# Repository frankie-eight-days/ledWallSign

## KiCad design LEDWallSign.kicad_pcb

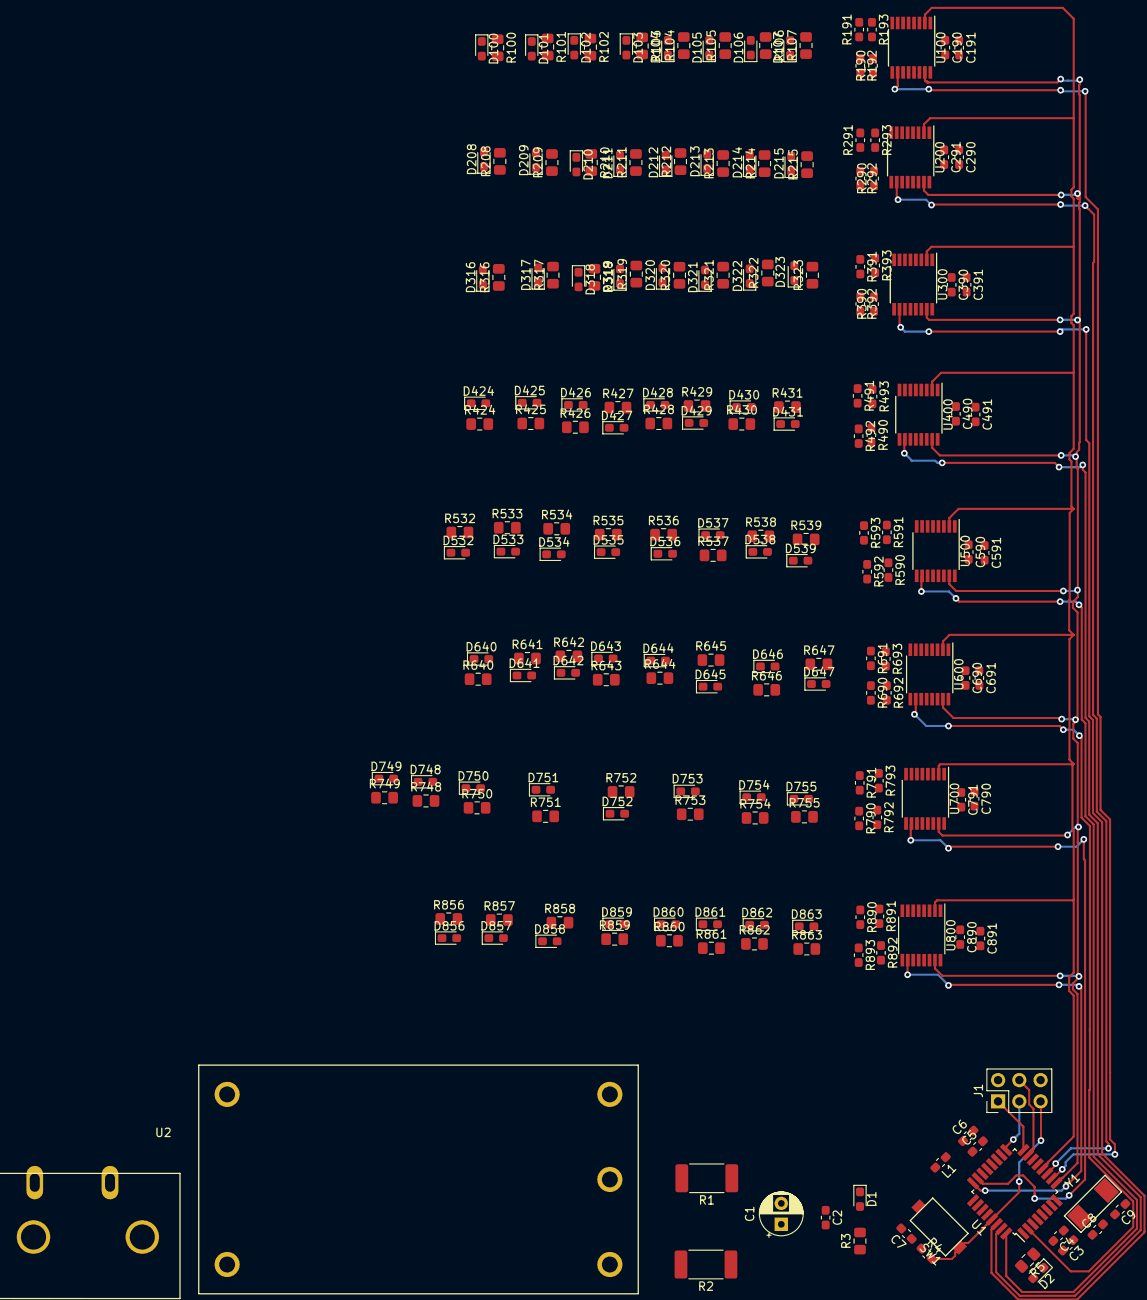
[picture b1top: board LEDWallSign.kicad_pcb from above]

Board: 2 copper layers, 207 parts (0 on the bottom side), 170 nets.

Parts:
C1: 10u; CP_Radial_D5.0mm_P2.50mm
C2, C4, C5, C7, C191, C291, C391, C491, C591, C691, C791, C891: 100nF; C_0603_1608Metric_Pad1.05x0.95mm_HandSolder
C3, C190, C290, C390, C490, C590, C690, C790, C890: 1uF; C_0603_1608Metric_Pad1.05x0.95mm_HandSolder
C6: 100pF; C_0603_1608Metric_Pad1.05x0.95mm_HandSolder
C8, C9: 18pF; C_0603_1608Metric_Pad1.05x0.95mm_HandSolder
D1, D2, D100, D101, D102, D103, D104, D105, D106, D107, D208, D209, D210, D211, D212, D213, D214, D215, D316, D317, D318, D319, D320, D321, D322, D323, D424, D425, D426, D427, D428, D429, D430, D431, D532, D533, D534, D535, D536, D537, D538, D539, D640, D641, D642, D643, D644, D645, D646, D647, D748, D749, D750, D751, D752, D753, D754, D755, D856, D857, D858, D859, D860, D861, D862, D863: LED; LED_0603_1608Metric_Pad1.05x0.95mm_HandSolder
J1: ISP Header; PinHeader_2x03_P2.54mm_Vertical
L1: Ferrite_Bead; L_0603_1608Metric_Pad1.05x0.95mm_HandSolder
P1: Conn_WallPlug; Qualtek 770W-X2
R1, R2: 0; R_2512_6332Metric_Pad1.52x3.35mm_HandSolder
R3, R5, R100, R101, R102, R103, R104, R105, R106, R107, R208, R209, R210, R211, R212, R213, R214, R215, R316, R317, R318, R319, R320, R321, R322, R323, R424, R425, R426, R427, R428, R429, R430, R431, R532, R533, R534, R535, R536, R537, R538, R539, R640, R641, R642, R643, R644, R645, R646, R647, R748, R749, R750, R751, R752, R753, R754, R755, R856, R857, R858, R859, R860, R861, R862, R863: 1k; R_0805_2012Metric_Pad1.15x1.40mm_HandSolder
R4, R190, R193, R290, R293, R390, R393, R490, R493, R590, R593, R690, R693, R790, R793, R890, R893: 10k; R_0603_1608Metric_Pad1.05x0.95mm_HandSolder
R191, R192, R291, R292, R391, R392, R491, R492, R591, R592, R691, R692, R791, R792, R891, R892: DNP; R_0603_1608Metric_Pad1.05x0.95mm_HandSolder
SW1: KSR251GLFS
U1: ATmega328-AU; TQFP-32_7x7mm_P0.8mm
U2: RAC10-05SK
U100, U200, U300, U400, U500, U600, U700, U800: TLC6C598-Q1; TSSOP-16_4.4x5mm_P0.65mm
Y1: 8MHz; ECS-23G

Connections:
+5V: C1.1, C2.2, C3.1, C4.1, C7.1, C190.1, C191.1, C290.1, C291.1, C390.1, C391.1, C490.1, C491.1, C590.1, C591.1, C690.1, C691.1, C790.1, C791.1, C890.1, C891.1, J1.2, L1.2, R2.1, R3.1, R4.1, R100.1, R101.1, R102.1, R103.1, R104.1, R105.1, R106.1, R107.1, R190.1, R191.1, R208.1, R209.1, R210.1, R211.1, R212.1, R213.1, R214.1, R215.1, R290.1, R291.1, R316.1, R317.1, R318.1, R319.1, R320.1, R321.1, R322.1, R323.1, R390.1, R391.1, R424.1, R425.1, R426.1, R427.1, R428.1, R429.1, R430.1, R431.1, R490.1, R491.1, R532.1, R533.1, R534.1, R535.1, R536.1, R537.1, R538.1, R539.1, R590.1, R591.1, R640.1, R641.1, R642.1, R643.1, R644.1, R645.1, R646.1, R647.1, R690.1, R691.1, R748.1, R749.1, R750.1, R751.1, R752.1, R753.1, R754.1, R755.1, R790.1, R791.1, R856.1, R857.1, R858.1, R859.1, R860.1, R861.1, R862.1, R863.1, R890.1, R891.1, U1.4, U1.6, U100.1, U200.1, U300.1, U400.1, U500.1, U600.1, U700.1, U800.1
+5VA: C5.1, C6.1, L1.1, U1.18, U1.20
/MISO: J1.1, U1.16
/MOSI: J1.4, U1.15
/SCK: J1.3, U1.17
/XTAL_IN: C8.1, U1.7, Y1.1
/XTAL_OUT: C9.1, U1.8, Y1.2
/blinky: R5.1, U1.1
/clockPin: U1.9, U100.15, U200.15, U300.15, U400.15, U500.15, U600.15, U700.15, U800.15
/dataPin: U1.12, U100.2, U200.2, U300.2, U400.2, U500.2, U600.2, U700.2, U800.2
/latch1: U1.10, U100.10
/latch2: U1.11, U200.10
/latch3: U1.30, U300.10
/latch4: U1.31, U400.10
/latch5: U1.32, U500.10
/latch6: U1.2, U600.10
/latch7: U1.23, U700.10
/latch8: U1.24, U800.10
/led0: D100.1, U100.3
/led1: D101.1, U100.4
/led2: D102.1, U100.5
/led3: D103.1, U100.6
/led4: D104.1, U100.11
/led5: D105.1, U100.12
/led6: D106.1, U100.13
/led7: D107.1, U100.14
/led8: D208.1, U200.3
/led9: D209.1, U200.4
/led10: D210.1, U200.5
/led11: D211.1, U200.6
/led12: D212.1, U200.11
/led13: D213.1, U200.12
/led14: D214.1, U200.13
/led15: D215.1, U200.14
/led16: D316.1, U300.3
/led17: D317.1, U300.4
/led18: D318.1, U300.5
/led19: D319.1, U300.6
/led20: D320.1, U300.11
/led21: D321.1, U300.12
/led22: D322.1, U300.13
/led23: D323.1, U300.14
/led24: D424.1, U400.3
/led25: D425.1, U400.4
/led26: D426.1, U400.5
/led27: D427.1, U400.6
/led28: D428.1, U400.11
/led29: D429.1, U400.12
/led30: D430.1, U400.13
/led31: D431.1, U400.14
/led32: D532.1, U500.3
/led33: D533.1, U500.4
/led34: D534.1, U500.5
/led35: D535.1, U500.6
/led36: D536.1, U500.11
/led37: D537.1, U500.12
/led38: D538.1, U500.13
/led39: D539.1, U500.14
/led40: D640.1, U600.3
/led41: D641.1, U600.4
/led42: D642.1, U600.5
/led43: D643.1, U600.6
/led44: D644.1, U600.11
/led45: D645.1, U600.12
/led46: D646.1, U600.13
/led47: D647.1, U600.14
/led48: D748.1, U700.3
/led49: D749.1, U700.4
/led50: D750.1, U700.5
/led51: D751.1, U700.6
/led52: D752.1, U700.11
/led53: D753.1, U700.12
/led54: D754.1, U700.13
/led55: D755.1, U700.14
/led56: D856.1, U800.3
/led57: D857.1, U800.4
/led58: D858.1, U800.5
/led59: D859.1, U800.6
/led60: D860.1, U800.11
/led61: D861.1, U800.12
/led62: D862.1, U800.13
/led63: D863.1, U800.14
/~RESET: J1.5, R4.2, SW1.1, U1.29
GND: C1.2, C2.1, C3.2, C4.2, C5.2, C6.2, C7.2, C8.2, C9.2, C190.2, C191.2, C290.2, C291.2, C390.2, C391.2, C490.2, C491.2, C590.2, C591.2, C690.2, C691.2, C790.2, C791.2, C890.2, C891.2, D1.1, D2.1, J1.6, R1.1, R192.2, R193.2, R292.2, R293.2, R392.2, R393.2, R492.2, R493.2, R592.2, R593.2, R692.2, R693.2, R792.2, R793.2, R892.2, R893.2, SW1.2, U1.3, U1.5, U1.21, U100.16, U200.16, U300.16, U400.16, U500.16, U600.16, U700.16, U800.16
unnamed: D1.2, R3.2
unnamed: D2.2, R5.2
unnamed: D100.2, R100.2
unnamed: D101.2, R101.2
unnamed: D102.2, R102.2
unnamed: D103.2, R103.2
unnamed: D104.2, R104.2
unnamed: D105.2, R105.2
unnamed: D106.2, R106.2
unnamed: D107.2, R107.2
unnamed: D208.2, R208.2
unnamed: D209.2, R209.2
unnamed: D210.2, R210.2
unnamed: D211.2, R211.2
unnamed: D212.2, R212.2
unnamed: D213.2, R213.2
unnamed: D214.2, R214.2
unnamed: D215.2, R215.2
unnamed: D316.2, R316.2
unnamed: D317.2, R317.2
unnamed: D318.2, R318.2
unnamed: D319.2, R319.2
unnamed: D320.2, R320.2
unnamed: D321.2, R321.2
unnamed: D322.2, R322.2
unnamed: D323.2, R323.2
unnamed: D424.2, R424.2
unnamed: D425.2, R425.2
unnamed: D426.2, R426.2
unnamed: D427.2, R427.2
unnamed: D428.2, R428.2
unnamed: D429.2, R429.2
unnamed: D430.2, R430.2
unnamed: D431.2, R431.2
unnamed: D532.2, R532.2
unnamed: D533.2, R533.2
unnamed: D534.2, R534.2
unnamed: D535.2, R535.2
unnamed: D536.2, R536.2
unnamed: D537.2, R537.2
unnamed: D538.2, R538.2
unnamed: D539.2, R539.2
unnamed: D640.2, R640.2
unnamed: D641.2, R641.2
unnamed: D642.2, R642.2
unnamed: D643.2, R643.2
unnamed: D644.2, R644.2
unnamed: D645.2, R645.2
unnamed: D646.2, R646.2
unnamed: D647.2, R647.2
unnamed: D748.2, R748.2
unnamed: D749.2, R749.2
unnamed: D750.2, R750.2
unnamed: D751.2, R751.2
unnamed: D752.2, R752.2
unnamed: D753.2, R753.2
unnamed: D754.2, R754.2
unnamed: D755.2, R755.2
unnamed: D856.2, R856.2
unnamed: D857.2, R857.2
unnamed: D858.2, R858.2
unnamed: D859.2, R859.2
unnamed: D860.2, R860.2
unnamed: D861.2, R861.2
unnamed: D862.2, R862.2
unnamed: D863.2, R863.2
unnamed: P1.1, U2.2
unnamed: P1.2, U2.1
unnamed: R1.2, U2.4
unnamed: R2.2, U2.5
unnamed: R190.2, R192.1, U100.7
unnamed: R191.2, R193.1, U100.8
unnamed: R290.2, R292.1, U200.7
unnamed: R291.2, R293.1, U200.8
unnamed: R390.2, R392.1, U300.7
unnamed: R391.2, R393.1, U300.8
unnamed: R490.2, R492.1, U400.7
unnamed: R491.2, R493.1, U400.8
unnamed: R590.2, R592.1, U500.7
unnamed: R591.2, R593.1, U500.8
unnamed: R690.2, R692.1, U600.7
unnamed: R691.2, R693.1, U600.8
unnamed: R790.2, R792.1, U700.7
unnamed: R791.2, R793.1, U700.8
unnamed: R890.2, R892.1, U800.7
unnamed: R891.2, R893.1, U800.8

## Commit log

2019-08-04 First commit
    Basic schematic done. Need to add footprints, references and complete BOM.
2019-08-05 References and footprints completed. Added back up layout (of components sorted)
    Going to play around with the layout now. Eventually hope to get final one done by end of this week.
2019-08-05 Fully organized parts into their subsystem categories. Also added new backup file for layout.
2019-08-06 did some stuff, a lil routing
